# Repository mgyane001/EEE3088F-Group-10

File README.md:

# EEE3088F Group 10 Micro-Mouse Project 2024

## Project Overview
The goal of the Micro-Mouse Project is designing and building a maze-solving robot, inspired by the principles and competition of Micro-Mouse robots. This project focuses on the hardware development of the robot, particularly the sensing and power subsystems, while integrating provided processor and motherboard modules.

### Components
- **Processor Module:** Utilizes a STM32L476 microcontroller for processing and programming.
- **Motherboard Module:** Serves as the foundational circuit board connecting all the other modules.
- **Sensing Module:** Designed to detect obstacles, aiding the robot in navigation.
- **Power Module:** Manages power distribution, motor operation, and battery charging.

## Installation & Setup
This section will guide you through setting up your development environment and assembling the Micro-Mouse robot.

### Prerequisites
- STM32CubeIDE for firmware development.
- Basic soldering equipment and electronic component handling knowledge.
- KiCad or any other electronics CAD software

### Assembly Instructions
1. **Processor & Motherboard Connection:** Start by connecting the processor module to the motherboard using the provided pin headers.
2. **Sensing Module Assembly:** Follow the schematic in `Docs/Sensing_Module_Schematic.pdf` to assemble your sensing module. Attach it to the motherboard as indicated.
3. **Power Module Assembly:** Assemble the power module according to `Docs/Power_Module_Schematic.pdf` and attach it to the designated motherboard location.
4. **Final Assembly:** Secure all connections and mount the assembled motherboard into the chassis and connect the motors and battery.

## Usage
To operate the Micro-Mouse:
1. **Firmware Upload:** Use STM32CubeIDE to open the project from `Firmware/` and flash it onto the processor module.
2. **Power On:** Switch on the Micro-Mouse using the power module's ON/OFF switch.
3. **Maze Testing:** Place the Micro-Mouse at the start of a maze and observe its operation and maze-solving capability.

## Contributing
We welcome contributions to the Micro-Mouse Project! If you have suggestions, improvements, or bug fixes, please follow the steps below:
1. Fork the repository.
2. Create a new branch (`git checkout -b feature/AmazingFeature`).
3. Commit your changes (`git commit -m 'Add some AmazingFeature'`).
4. Push to the branch (`git push origin feature/AmazingFeature`).
5. Open a pull request.

## Project Structure
- `/Firmware`: Contains all firmware code for the Micro-Mouse.
- `/Docs`: Documentation, including module schematics and assembly guides.
- `/Tools`: Auxiliary tools for development and testing.
- `/Designs`: CAD designs for optional chassis and mechanical parts.

## Support
For support, please open an issue in the repository or contact the project maintainers directly via email.

## Acknowledgements
- **Veritasium:** For the inspirational content on Micro-Mouse robots.
- **STM32L476 Community:** For resources and support in firmware development.

## License
This project is licensed under the MIT License - see the `LICENSE` file for details.

---

We hope this project inspires and educates all participants and observers alike. Happy building!

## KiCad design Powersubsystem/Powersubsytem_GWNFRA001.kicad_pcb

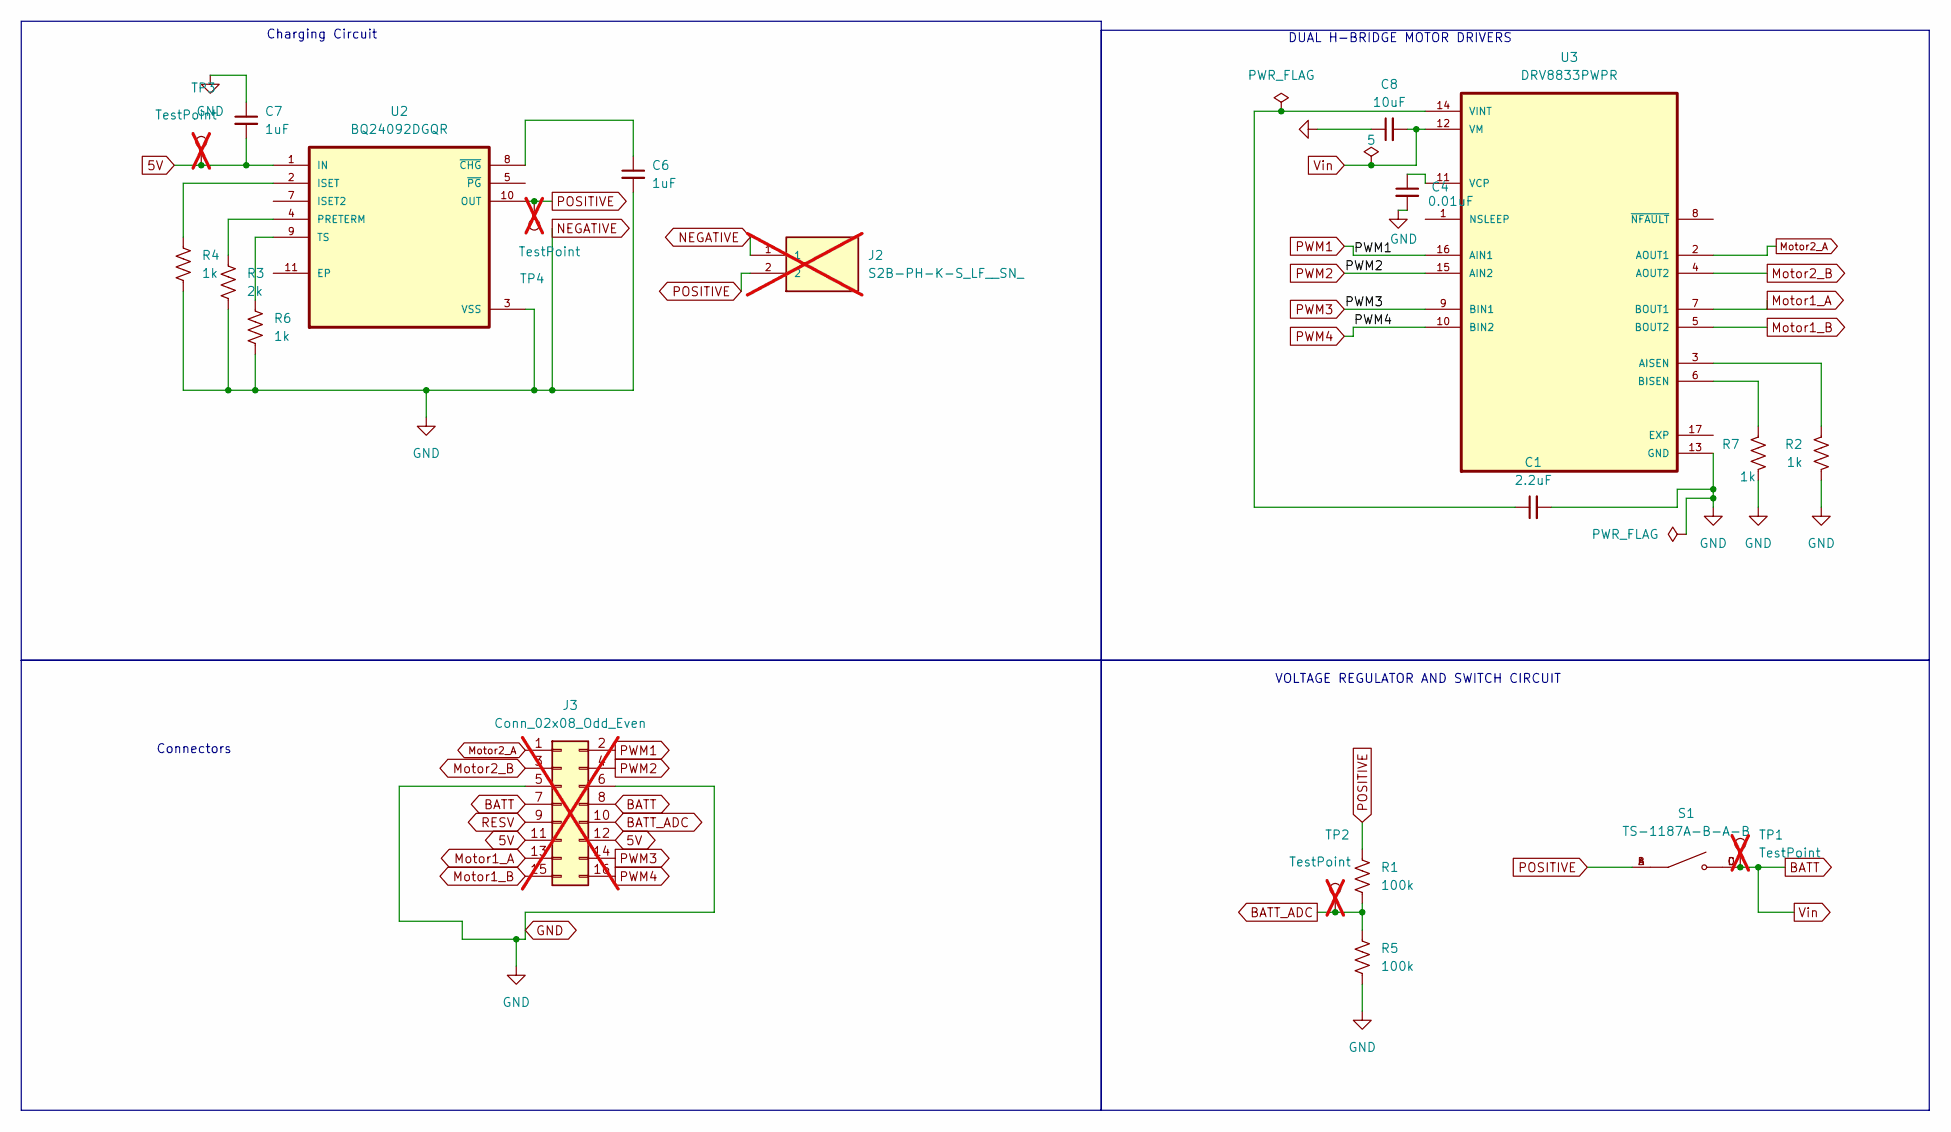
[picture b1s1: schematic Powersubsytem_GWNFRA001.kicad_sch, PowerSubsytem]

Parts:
C1: 2.2uF; C_0402_1005Metric
C4: 0.01uF; C_01005_0402Metric
C6, C7: 1uF; C_0402_1005Metric
C8: 10uF; C_0402_1005Metric
J2: S2B-PH-K-S_LF__SN_; JST_S2B-PH-K-S_LF__SN_; not fitted
J3: Conn_02x08_Odd_Even; PinHeader_2x08_P2.54mm_Vertical; not fitted
R1, R5: 100k; BO_CR0603
R2, R4, R6, R7: 1k; BO_CR0603
R3: 2k; BO_CR0603
S1: TS-1187A-B-A-B; SW_TS-1187A-B-A-B; PARTREV A0
TP1, TP2, TP3, TP4: TestPoint; TestPoint_THTPad_D1.0mm_Drill0.5mm; not fitted
U2: BQ24092DGQR; IC_XTR111AIDGQR
U3: DRV8833PWPR; IC_DRV8833PWPR; PARTREV E; LCSC C50506

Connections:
5V: C7.2, J3.11, J3.12, TP3.1, U2.1 (IN)
BATT: C8.2, J3.7, J3.8, S1.C, S1.D, TP1.1, U3.12 (VM)
BATT_ADC: J3.10, R1.2, R5.1, TP2.1
GND: C1.2, C4.2, C6.2, C7.1, C8.1, J2.1, J3.5, J3.6, R2.2, R3.2, R4.2, R5.2, R6.2, R7.2, U2.3 (VSS), U3.13 (GND)
Motor1_A: J3.13, U3.7 (BOUT1)
Motor1_B: J3.15, U3.5 (BOUT2)
Motor2_A: J3.1, U3.2 (AOUT1)
Motor2_B: J3.3, U3.4 (AOUT2)
unnamed: R4.1, U2.2 (ISET)
unnamed: R3.1, U2.4 (PRETERM)
unnamed: R6.1, U2.9 (TS)
unnamed: C6.1, U2.8 (~CHG)
unnamed: R2.1, U3.3 (AISEN)
unnamed: R7.1, U3.6 (BISEN)
unnamed: C4.1, U3.11 (VCP)
unnamed: C1.1, U3.14 (VINT)
POSITIVE: J2.2, R1.1, S1.A, S1.B, TP4.1, U2.10 (OUT)
PWM1: J3.2, U3.16 (AIN1)
PWM2: J3.4, U3.15 (AIN2)
PWM3: J3.14, U3.9 (BIN1)
PWM4: J3.16, U3.10 (BIN2)
RESV: J3.9

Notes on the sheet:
Charging Circuit
VOLTAGE REGULATOR AND SWITCH CIRCUIT
Connectors
DUAL H-BRIDGE MOTOR DRIVERS

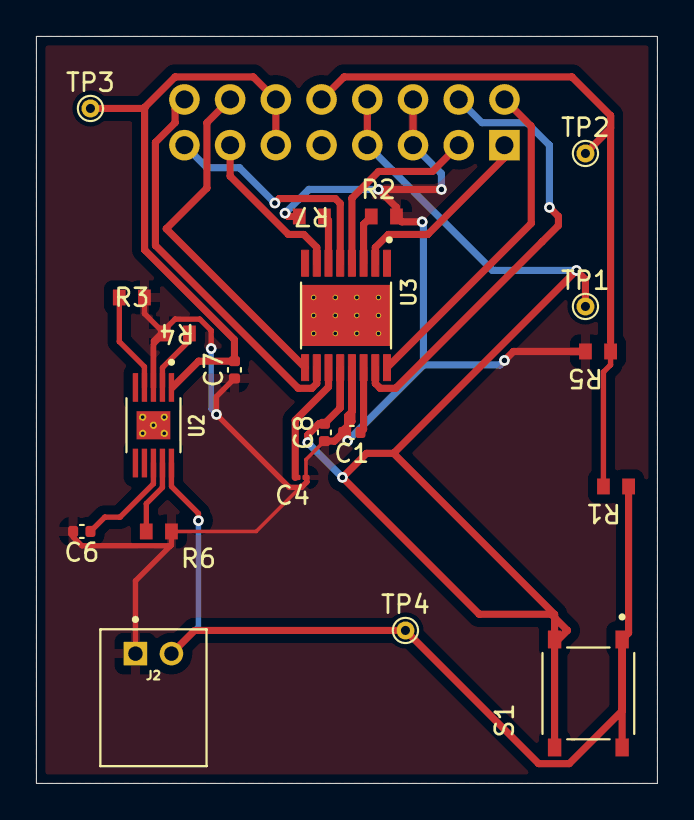
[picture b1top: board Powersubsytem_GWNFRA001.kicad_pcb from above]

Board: 2 copper layers, 34.5 x 41.5 mm, 21 parts (1 on the bottom side), 21 nets.

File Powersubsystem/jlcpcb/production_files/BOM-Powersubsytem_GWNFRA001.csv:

Comment,Designator,Footprint,LCSC
2.2uF,C1,C_0402_1005Metric,C12530
BQ24092DGQR,U2,IC_XTR111AIDGQR,C133237
10uF,C8,C_0402_1005Metric,C15195
1k,"R2,R4,R6,R7",BO_CR0603,C21190
2k,R3,BO_CR0603,C22975
100k,"R1,R5",BO_CR0603,C25803
TS-1187A-B-A-B,S1,SW_TS-1187A-B-A-B,C318884
DRV8833PWPR,U3,IC_DRV8833PWPR,C50506
1uF,"C6,C7",C_0402_1005Metric,C52923
0.01uF,C4,C_01005_0402Metric,

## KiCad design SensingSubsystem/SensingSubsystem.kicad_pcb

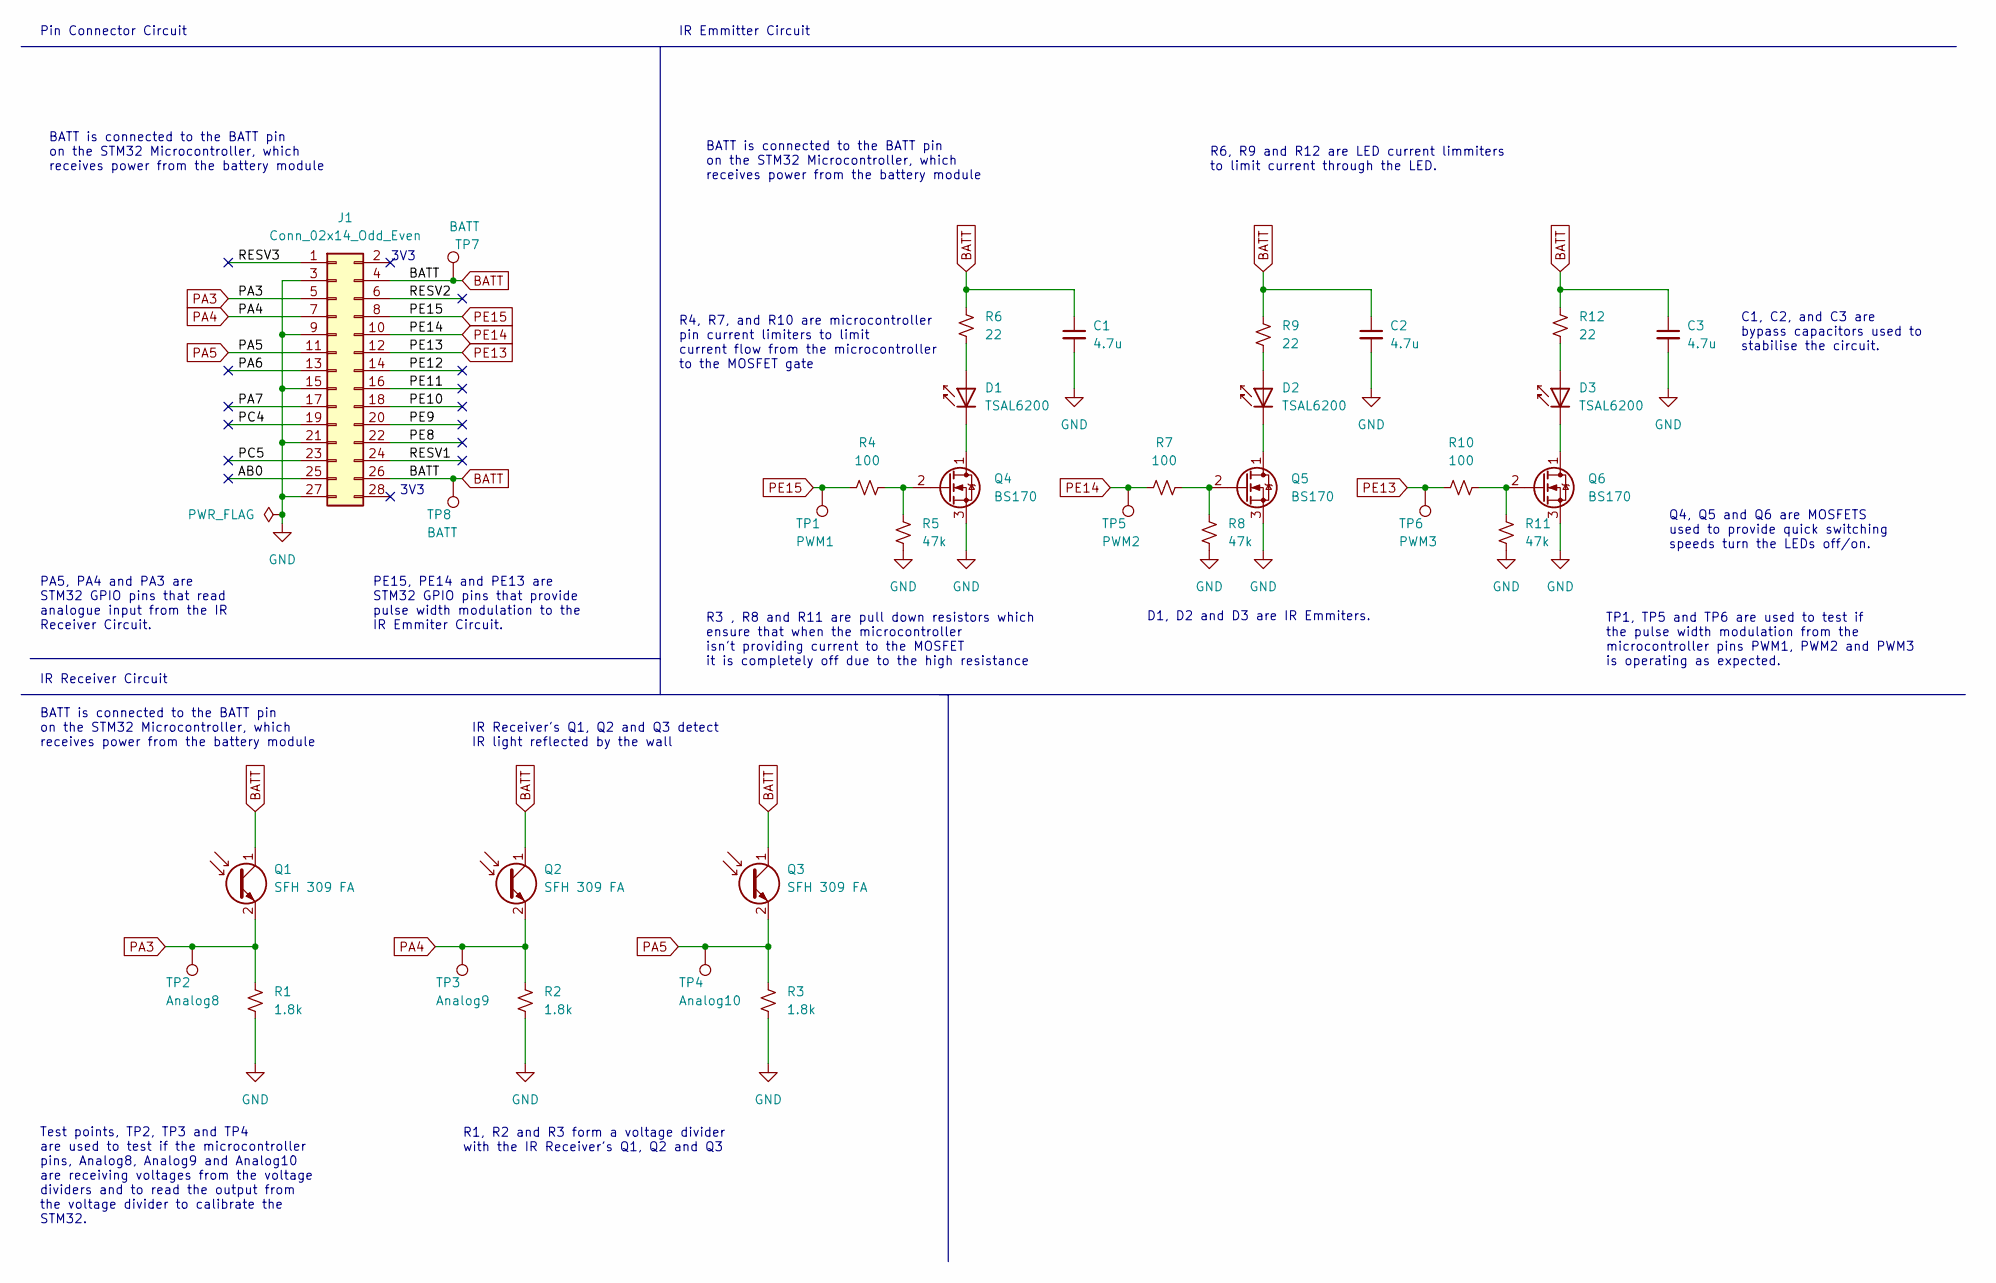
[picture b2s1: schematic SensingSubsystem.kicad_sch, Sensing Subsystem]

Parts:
C1, C2, C3: 4.7u; C_0805_2012Metric
D1, D2, D3: TSAL6200; LED_D5.0mm_Horizontal_O1.27mm_Z15.0mm
J1: Conn_02x14_Odd_Even; PinHeader_2x14_P2.54mm_Vertical
Q1, Q2, Q3: SFH 309 FA; LED_D3.0mm_Horizontal_O1.27mm_Z10.0mm
Q4, Q5, Q6: BS170; TO-92_Inline
R1, R2, R3: 1.8k; R_0603_1608Metric
R4, R7, R10: 100; R_0603_1608Metric
R5, R8, R11: 47k; R_0603_1608Metric
R6, R9, R12: 22; R_0603_1608Metric
TP1: PWM1; TestPoint_THTPad_D1.0mm_Drill0.5mm
TP2: Analog8; TestPoint_THTPad_D1.0mm_Drill0.5mm
TP3: Analog9; TestPoint_THTPad_D1.0mm_Drill0.5mm
TP4: Analog10; TestPoint_THTPad_D1.0mm_Drill0.5mm
TP5: PWM2; TestPoint_THTPad_D1.0mm_Drill0.5mm
TP6: PWM3; TestPoint_THTPad_D1.0mm_Drill0.5mm
TP7, TP8: BATT; TestPoint_THTPad_D1.0mm_Drill0.5mm

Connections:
/AB0: J1.25
/PA6: J1.13
/PA7: J1.17
/PC4: J1.19
/PC5: J1.23
/PE8: J1.22
/PE9: J1.20
/PE10: J1.18
/PE11: J1.16
/PE12: J1.14
/RESV1: J1.24
/RESV2: J1.6
/RESV3: J1.1
BATT: C1.1, C2.1, C3.1, J1.4, J1.26, Q1.1 (C), Q2.1 (C), Q3.1 (C), R6.1, R9.1, R12.1, TP7.1, TP8.1
GND: C1.2, C2.2, C3.2, J1.3, J1.9, J1.15, J1.21, J1.27, Q4.3 (S), Q5.3 (S), Q6.3 (S), R1.2, R2.2, R3.2, R5.1, R8.1, R11.1
unnamed: D1.1 (K), Q4.1 (D)
unnamed: D1.2 (A), R6.2
unnamed: D2.1 (K), Q5.1 (D)
unnamed: D2.2 (A), R9.2
unnamed: D3.1 (K), Q6.1 (D)
unnamed: D3.2 (A), R12.2
unnamed: Q4.2 (G), R4.2, R5.2
unnamed: Q5.2 (G), R7.2, R8.2
unnamed: Q6.2 (G), R10.2, R11.2
PA3: J1.5, Q1.2 (E), R1.1, TP2.1
PA4: J1.7, Q2.2 (E), R2.1, TP3.1
PA5: J1.11, Q3.2 (E), R3.1, TP4.1
PE13: J1.12, R10.1, TP6.1
PE14: J1.10, R7.1, TP5.1
PE15: J1.8, R4.1, TP1.1

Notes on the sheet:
R3 , R8 and R11 are pull down resistors which ensure that when the microcontroller isn't providing current to the MOSFET it is completely off due to the high resistance
IR Emmitter Circuit
C1, C2, and C3 are bypass capacitors used to stabilise the circuit.
PE15, PE14 and PE13 are STM32 GPIO pins that provide pulse width modulation to the IR Emmiter Circuit.
3V3
R6, R9 and R12 are LED current limmiters to limit current through the LED.
TP1, TP5 and TP6 are used to test if the pulse width modulation from the microcontroller pins PWM1, PWM2 and PWM3 is operating as expected.
BATT is connected to the BATT pin on the STM32 Microcontroller, which receives power from the battery module
Test points, TP2, TP3 and TP4 are used to test if the microcontroller pins, Analog8, Analog9 and Analog10 are receiving voltages from the voltage dividers and to read the output from the voltage divider to calibrate the STM32.
Pin Connector Circuit
PA5, PA4 and PA3 are STM32 GPIO pins that read analogue input from the IR Receiver Circuit.
IR Receiver's Q1, Q2 and Q3 detect IR light reflected by the wall
D1, D2 and D3 are IR Emmiters.
IR Receiver Circuit
Q4, Q5 and Q6 are MOSFETS used to provide quick switching speeds turn the LEDs off/on.
R4, R7, and R10 are microcontroller pin current limiters to limit current flow from the microcontroller to the MOSFET gate
R1, R2 and R3 form a voltage divider with the IR Receiver's Q1, Q2 and Q3

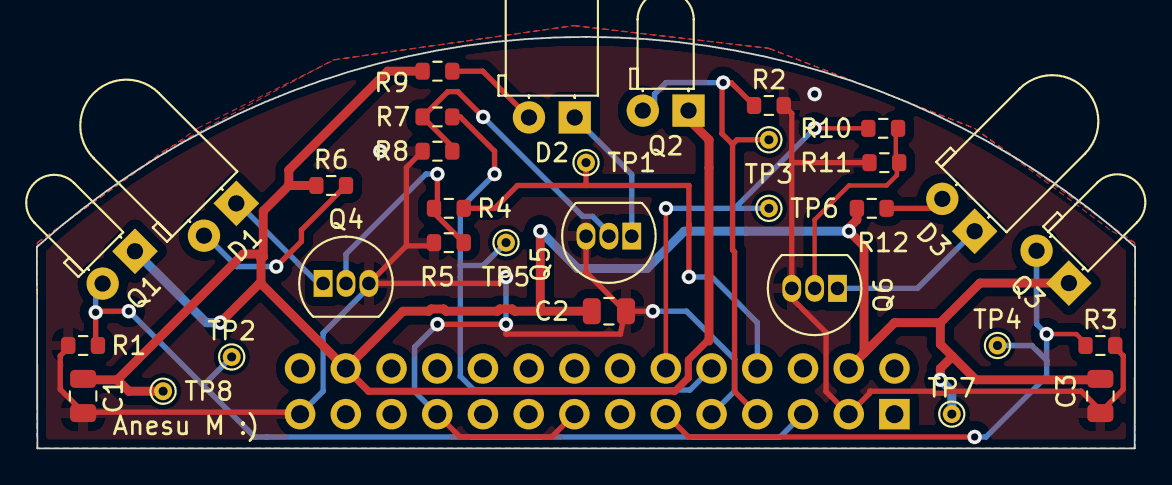
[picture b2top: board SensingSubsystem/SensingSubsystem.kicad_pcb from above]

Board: 2 copper layers, 61.0 x 22.9 mm, 33 parts (1 on the bottom side), 17 nets.

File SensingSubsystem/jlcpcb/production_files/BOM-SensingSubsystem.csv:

Comment,Designator,Footprint,LCSC
BS170,"Q4,Q5,Q6",TO-92_Inline,C111691
4.7u,"C1,C2,C3",C_0805_2012Metric,C19666
100,"R10,R4,R7",R_0603_1608Metric,C22775
22,"R12,R6,R9",R_0603_1608Metric,C23345
47k,"R11,R5,R8",R_0603_1608Metric,C25819
SFH 309 FA,"Q1,Q2,Q3",LED_D3.0mm_Horizontal_O1.27mm_Z10.0mm,C2900253
1.8k,"R1,R2,R3",R_0603_1608Metric,C4177
TSAL6200,"D1,D2,D3",LED_D5.0mm_Horizontal_O1.27mm_Z15.0mm,C55528

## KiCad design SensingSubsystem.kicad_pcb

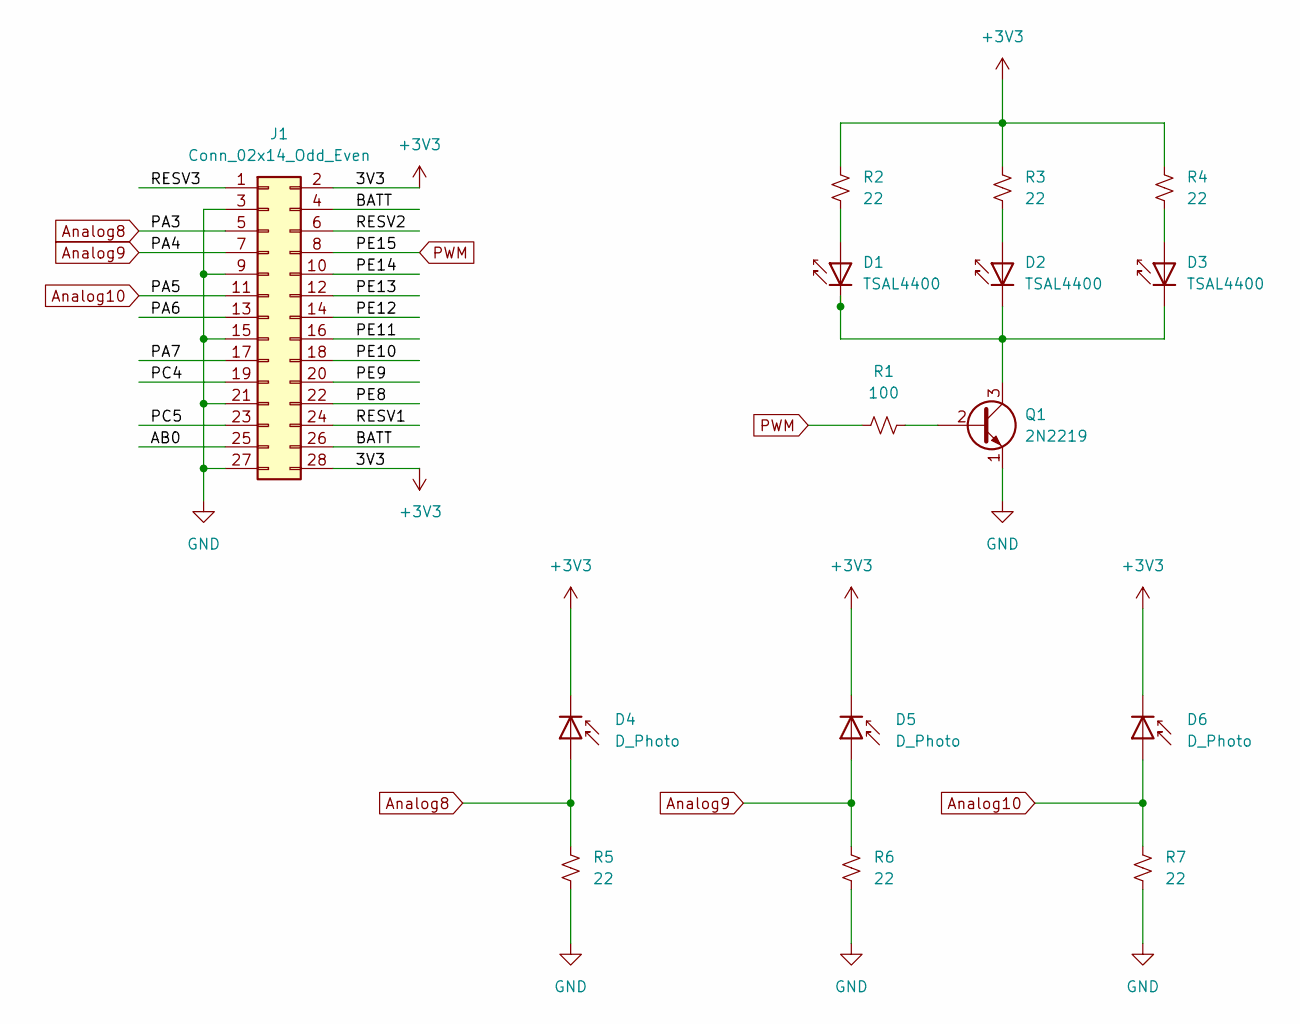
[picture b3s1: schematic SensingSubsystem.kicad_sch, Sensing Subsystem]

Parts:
D1, D2, D3: TSAL4400; LED_D3.0mm_Horizontal_O1.27mm_Z2.0mm
D4, D5, D6: D_Photo; Osram_SFH205
J1: Conn_02x14_Odd_Even; PinHeader_2x14_P2.54mm_Vertical
Q1: 2N2219; TO-39-3
R1: 100; R_0201_0603Metric
R2, R3, R4, R5, R6, R7: 22; R_0201_0603Metric

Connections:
+3V3: D4.1 (K), D5.1 (K), D6.1 (K), J1.2, J1.28, R2.1, R3.1, R4.1; also elsewhere on the board
/AB0: J1.25
/BATT: J1.4, J1.26
/PA6: J1.13
/PA7: J1.17
/PC4: J1.19
/PC5: J1.23
/PE8: J1.22
/PE9: J1.20
/PE10: J1.18
/PE11: J1.16
/PE12: J1.14
/PE13: J1.12
/PE14: J1.10
/RESV1: J1.24
/RESV2: J1.6
/RESV3: J1.1
Analog8: D4.2 (A), J1.5, R5.1
Analog9: D5.2 (A), J1.7, R6.1; also elsewhere on the board
Analog10: D6.2 (A), J1.11, R7.1
GND: J1.3, J1.9, J1.15, J1.21, J1.27, Q1.1 (E), R5.2, R6.2, R7.2
unnamed: D1.1 (K), D2.1 (K), D3.1 (K), Q1.3 (C)
unnamed: D1.2 (A), R2.2
unnamed: D2.2 (A), R3.2
unnamed: D3.2 (A), R4.2
unnamed: Q1.2 (B), R1.2
PWM: J1.8, R1.1

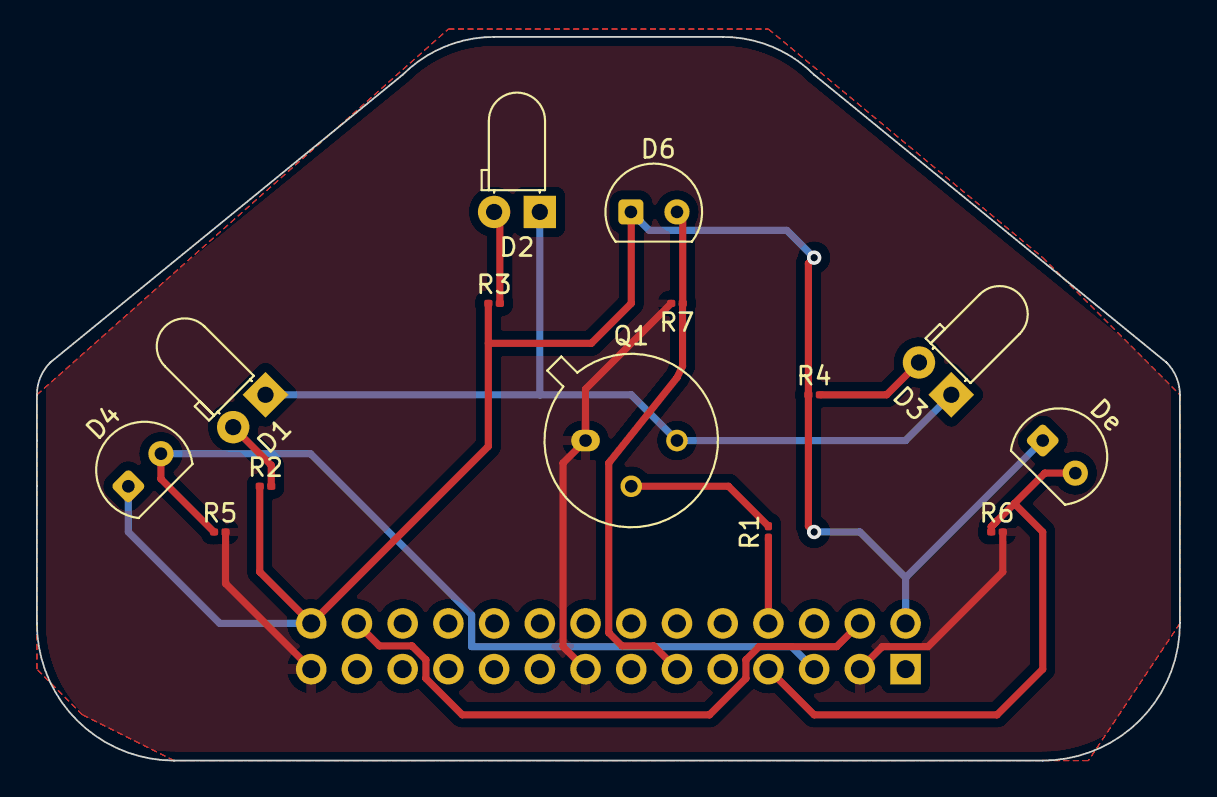
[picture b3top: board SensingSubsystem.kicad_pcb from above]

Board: 2 copper layers, 63.5 x 40.2 mm, 15 parts (1 on the bottom side), 12 nets.

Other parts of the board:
De: D_Photo; Osram_SFH205

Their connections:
+3V3: De.1 (K); also elsewhere on the board
Analog9: De.2 (A); also elsewhere on the board

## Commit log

2024-03-23 Create README
    Made the README File
2024-03-23 Update and rename README to README.md
    Changed the name of the file
2024-03-23 Prototype Circuit for Sensing Subsystem
2024-04-16 Sensing subsystem initial commit
2024-04-20 Create instructions
2024-04-20 Power Subsystem
